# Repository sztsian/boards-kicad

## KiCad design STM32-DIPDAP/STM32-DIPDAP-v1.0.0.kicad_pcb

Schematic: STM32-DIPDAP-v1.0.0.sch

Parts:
C1, C3, C7, C8, C9, C10, C11, C12: 100nF; C_0805_2012Metric_Pad1.15x1.40mm_HandSolder
C2, C4: 10uF; C_0603_1608Metric_Pad1.05x0.95mm_HandSolder
C5, C6: 22pF; C_0603_1608Metric_Pad1.05x0.95mm_HandSolder
C13, C14: 18pF; C_0805_2012Metric_Pad1.15x1.40mm_HandSolder
CON1: USB_B_Micro; USB_Micro-B_Connector
CON2: IF; PinHeader_1x05_P2.54mm_Vertical
CON4: SWD-10-SMD; Connector_2x05_P2.54mm_Edge
CON5: GROVE-UART-I2C-PTH; PinHeader_1x04_P2.54mm_Vertical
LED1: RED; LED_0805_2012Metric_Pad1.15x1.40mm_HandSolder
LED2: BLUE; LED_0805_2012Metric_Pad1.15x1.40mm_HandSolder
LED3: GREEN; LED_0805_2012Metric_Pad1.15x1.40mm_HandSolder
R1, R11: 10K; R_0805_2012Metric_Pad1.15x1.40mm_HandSolder
R2, R14: 100K; R_0805_2012Metric_Pad1.15x1.40mm_HandSolder
R3, R5: 4.7K; R_0805_2012Metric_Pad1.15x1.40mm_HandSolder
R4, R7: 33R; R_0603_1608Metric_Pad1.05x0.95mm_HandSolder
R6: 100R; R_0603_1608Metric_Pad1.05x0.95mm_HandSolder
R8: 470R; R_0603_1608Metric_Pad1.05x0.95mm_HandSolder
R9, R10: 1.5K; R_0805_2012Metric_Pad1.15x1.40mm_HandSolder
SW1: SKRKAEE010
TP1, TP2, TP3, TP4, TP5, TP6, TP7, TP8: PTR1TP07R; TP07R
U2: TLV1117LV33DCYR; SOT223
U3: STM32F103CBT6; LQFP-48_7x7mm_P0.5mm
Y1: 8M; Crystal_SMD_5032-2Pin_5.0x3.2mm

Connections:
+3.3V: C3.1, C4.1, C8.1, C9.1, C10.1, C11.1, CON2.4, CON5.3, LED2.2, LED3.2, R2.1, R3.1, R11.1, U2.OUT(1), U2.OUT(2), U3.1, U3.9, U3.24, U3.36, U3.48
/AIN12_1: TP2.TP, U3.11
/AIN12_9: TP1.TP, U3.19
/I2C1_SCL: TP4.TP, U3.45
/I2C1_SDA: TP3.TP, U3.46
/I2C2_SCL: CON5.1, U3.21
/I2C2_SDA: CON5.2, U3.22
/IF_NRESET: C7.1, CON2.5, R2.2, U3.7
/IF_SWCLK: CON2.2, U3.37
/IF_SWDIO: CON2.1, U3.34
/LED_COM_GRN: R10.2, U3.41
/LED_DAP_BLUE: R9.2, U3.42
/LED_PWR_RED: R8.2, U3.30
/SPI1_MISO: TP8.TP, U3.16
/SPI1_MOSI: TP7.TP, U3.17
/SPI1_NSS: TP5.TP, U3.14
/SPI1_SCK: TP6.TP, U3.39
/TGT_NRESET: C12.1, CON4.10, R11.2, SW1.P$1, U3.18
/TGT_RX: CON4.8, U3.12
/TGT_SWCLK: CON4.4, U3.15, U3.26
/TGT_SWDIO: CON4.2, R6.2, U3.27
/TGT_SWO: CON4.6, U3.31
/TGT_TX: CON4.7, U3.13
/TGT_USB_D+: CON1.3 (D+), R4.2
/TGT_USB_D-: CON1.2 (D-), R7.2
GND: C1.2, C2.2, C3.2, C4.2, C5.2, C6.2, C7.2, C8.2, C9.2, C10.2, C11.2, C12.2, C13.2, C14.2, CON1.5 (GND), CON2.3, CON4.3, CON4.5, CON4.9, CON5.4, LED1.1, R1.1, R5.2, R14.1, SW1.P$2, U2.GND, U3.8, U3.20, U3.23, U3.35, U3.47
unnamed: C1.1, C2.1, CON1.1 (VBUS), U2.IN
unnamed: C5.1, U3.5, Y1.1
unnamed: C6.1, U3.6, Y1.2
unnamed: C13.1, R7.1, U3.32
unnamed: C14.1, R4.1, U3.33
unnamed: LED1.2, R8.1
unnamed: LED2.1, R9.1
unnamed: LED3.1, R10.1
unnamed: R1.2, U3.2
unnamed: R3.2, R5.1, U3.10
unnamed: R6.1, U3.25
unnamed: R14.2, U3.44

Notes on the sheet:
8MHz
DAPLink Interface STM32F103CBT6

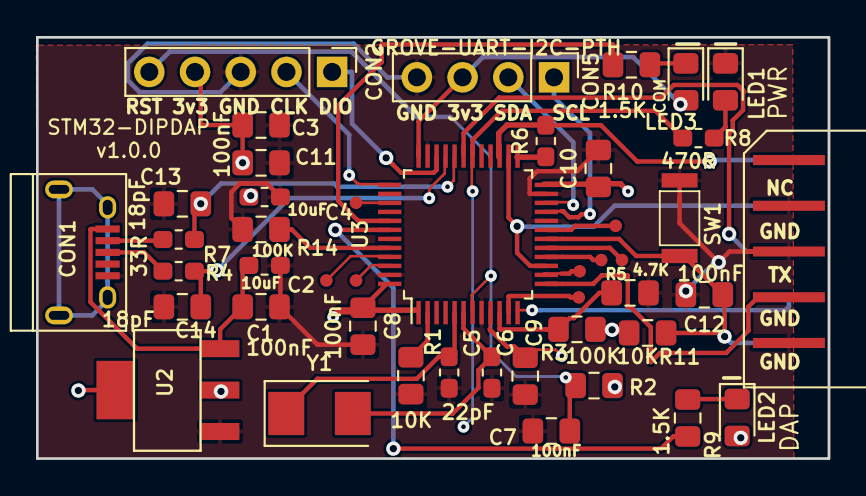
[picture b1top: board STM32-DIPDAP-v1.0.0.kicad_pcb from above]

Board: 2 copper layers, 44.0 x 23.4 mm, 45 parts (0 on the bottom side), 38 nets.

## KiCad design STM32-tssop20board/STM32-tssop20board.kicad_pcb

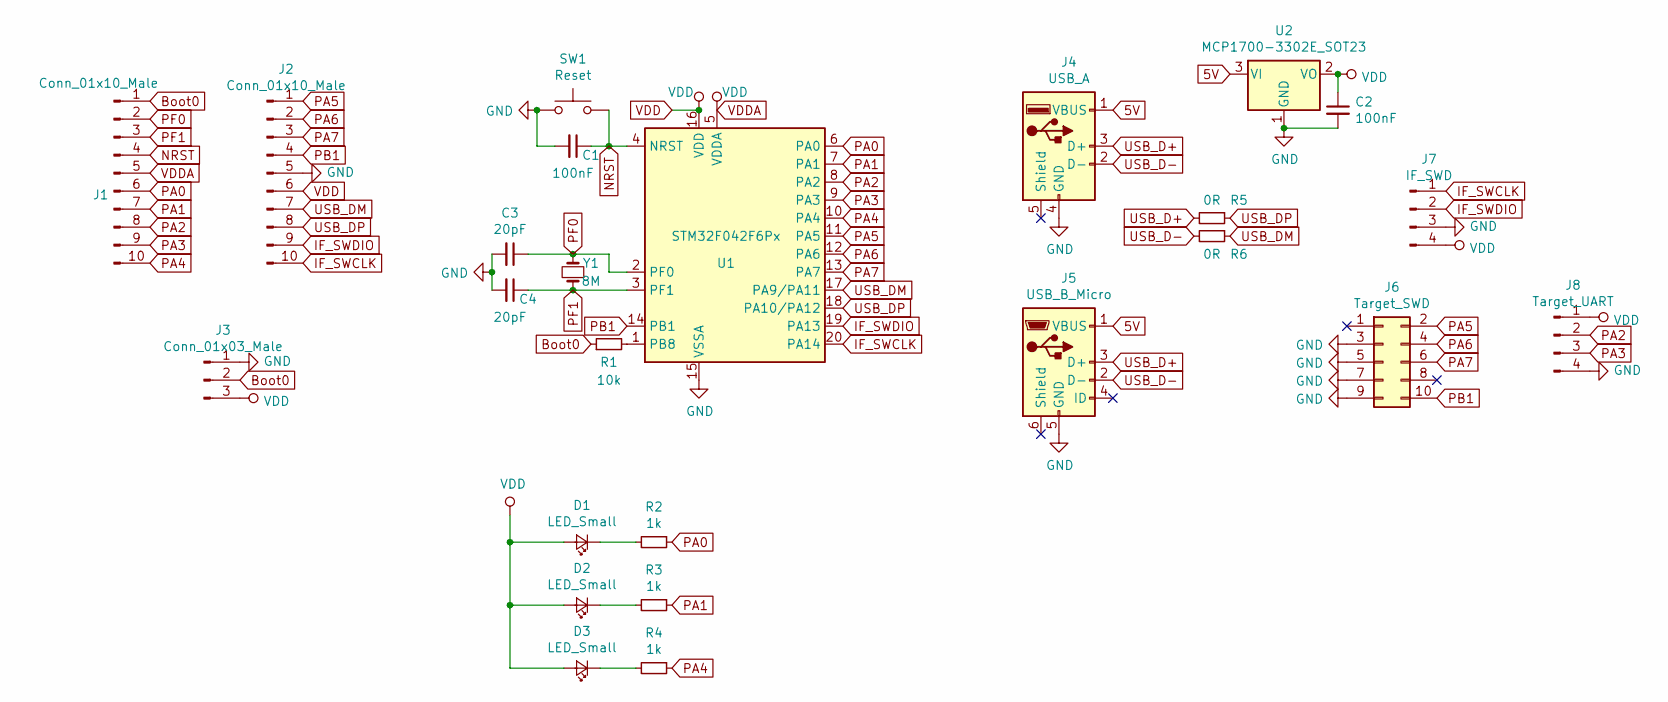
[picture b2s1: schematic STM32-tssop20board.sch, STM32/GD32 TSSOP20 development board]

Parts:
C1, C2: 100nF; C_0805_2012Metric_Pad1.15x1.40mm_HandSolder
C3, C4: 20pF; C_0805_2012Metric_Pad1.15x1.40mm_HandSolder
D1, D2, D3: LED_Small; LED_0805_2012Metric_Pad1.15x1.40mm_HandSolder
J1, J2: Conn_01x10_Male; PinHeader_1x10_P2.54mm_Vertical
J3: Conn_01x03_Male; PinHeader_1x03_P2.54mm_Vertical
J4: USB_A; USB_A_Plug
J5: USB_B_Micro; USB_Micro-B_Wuerth_614105150721_Vertical
J6: Target_SWD; PinHeader_2x05_P2.54mm_Vertical
J7: IF_SWD; PinHeader_1x04_P2.54mm_Vertical
J8: Target_UART; PinHeader_1x04_P2.54mm_Vertical
R1: 10k; R_0805_2012Metric_Pad1.15x1.40mm_HandSolder
R2, R3, R4: 1k; R_0805_2012Metric_Pad1.15x1.40mm_HandSolder
R5, R6: 0R; R_0805_2012Metric_Pad1.15x1.40mm_HandSolder
SW1: Reset; smd_push
U1: STM32F042F6Px; TSSOP-20_4.4x6.5mm_P0.65mm
U2: MCP1700-3302E_SOT23; SOT-23
Y1: 8M; Crystal_SMD_5032-2Pin_5.0x3.2mm_HandSoldering

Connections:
5V: J4.1 (VBUS), J5.1 (VBUS), U2.3 (VI)
Boot0: J1.1, J3.2, R1.1
GND: C1.2, C2.2, C3.2, C4.2, J2.5, J3.1, J4.4 (GND), J5.5 (GND), J6.3, J6.5, J6.7, J6.9, J7.3, J8.4, SW1.1, U1.15 (VSSA), U2.1 (GND)
IF_SWCLK: J2.10, J7.1, U1.20 (PA14)
IF_SWDIO: J2.9, J7.2, U1.19 (PA13)
NRST: C1.1, J1.4, SW1.2, U1.4 (NRST)
unnamed: D1.1 (K), R2.2
unnamed: D2.1 (K), R3.2
unnamed: D3.1 (K), R4.2
unnamed: R1.2, U1.1 (PB8)
PA0: J1.6, R2.1, U1.6 (PA0)
PA1: J1.7, R3.1, U1.7 (PA1)
PA2: J1.8, J8.2, U1.8 (PA2)
PA3: J1.9, J8.3, U1.9 (PA3)
PA4: J1.10, R4.1, U1.10 (PA4)
PA5: J2.1, J6.2, U1.11 (PA5)
PA6: J2.2, J6.4, U1.12 (PA6)
PA7: J2.3, J6.6, U1.13 (PA7)
PB1: J2.4, J6.10, U1.14 (PB1)
PF0: C3.1, J1.2, U1.2 (PF0), Y1.2
PF1: C4.1, J1.3, U1.3 (PF1), Y1.1
USB_D+: J4.3 (D+), J5.3 (D+), R5.2
USB_D-: J4.2 (D-), J5.2 (D-), R6.2
USB_DM: J2.7, R6.1, U1.17 (PA9/PA11)
USB_DP: J2.8, R5.1, U1.18 (PA10/PA12)
VDD: C2.1, D1.2 (A), D2.2 (A), D3.2 (A), J1.5, J2.6, J3.3, J7.4, J8.1, U1.5 (VDDA), U1.16 (VDD), U2.2 (VO)

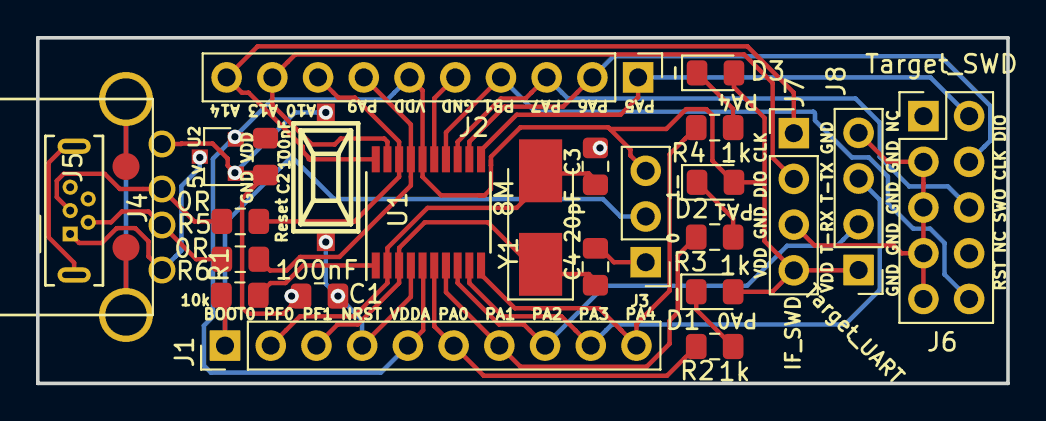
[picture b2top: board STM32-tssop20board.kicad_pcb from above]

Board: 2 copper layers, 53.9 x 19.2 mm, 25 parts (0 on the bottom side), 26 nets.

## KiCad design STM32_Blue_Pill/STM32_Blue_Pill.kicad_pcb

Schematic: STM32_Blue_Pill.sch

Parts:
C1, C2, C3, C11: 20p; C_0603_1608Metric_Pad1.05x0.95mm_HandSolder
C4: 1u; C_0603_1608Metric_Pad1.05x0.95mm_HandSolder
C5, C6, C7: 0.1u; C_0603_1608Metric_Pad1.05x0.95mm_HandSolder
C8: 10n; C_0603_1608Metric_Pad1.05x0.95mm_HandSolder
C9: 2.2u; C_0603_1608Metric_Pad1.05x0.95mm_HandSolder
C10: 100nF; C_0603_1608Metric_Pad1.05x0.95mm_HandSolder
D1: LED2; LED_0603_1608Metric_Pad1.05x0.95mm_HandSolder
D2: LED_PWR; LED_0603_1608Metric_Pad1.05x0.95mm_HandSolder
J1: BootJumper; PinHeader_2x03_P2.54mm_Vertical
J2, J3: Conn_01x20; PinHeader_1x20_P2.54mm_Vertical
J4: Conn_02x05_Odd_Even; PinHeader_2x05_P2.54mm_Horizontal
J7: USB_B_Micro; USB_Micro-B_Connector
R1, R2: 510R; R_0603_1608Metric_Pad1.05x0.95mm_HandSolder
R3: 1M; R_0603_1608Metric_Pad1.05x0.95mm_HandSolder
R4: 1.5K; R_0603_1608Metric_Pad1.05x0.95mm_HandSolder
R5: 10k; R_0603_1608Metric_Pad1.05x0.95mm_HandSolder
R7: 0R; R_0805_2012Metric_Pad1.15x1.40mm_HandSolder
R9, R10: 22; R_0603_1608Metric_Pad1.05x0.95mm_HandSolder
SW1: SW_Push; smd_push
U1: MCP1700-3302E_SOT23; SOT-23
U4: STM32F103C8Tx; LQFP-48_7x7mm_P0.5mm
Y1: 8M; Crystal_SMD_5032-2Pin_5.0x3.2mm
Y2: 32.768K; Crystal_SMD_3215-2Pin_3.2x1.5mm

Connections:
5V: J3.3, J7.1 (VBUS), R4.2, U1.3
BOOT0: J1.3, U4.44 (BOOT0)
BOOT1: J1.4, U4.20 (PB2)
GND: C1.2, C2.2, C3.2, C4.1, C5.1, C6.1, C7.1, C8.2, C9.2, C10.2, C11.2, J1.5, J1.6, J2.19, J2.20, J3.2, J4.3, J4.5, J7.5 (GND), J7.6 (Shield), R2.2, SW1.2, U1.1, U4.8 (VSSA), U4.23 (VSS), U4.35 (VSS), U4.47 (VSS)
NRST: C4.2, J2.17, J4.10, R5.1, SW1.1, U4.7 (NRST)
unnamed: C2.1, R3.1, U4.5 (PD0), Y1.1
unnamed: C3.1, R3.2, U4.6 (PD1), Y1.2
unnamed: C8.1, C9.1, R7.2, U4.9 (VDDA)
unnamed: D1.1 (K), R1.1
unnamed: D2.1 (K), R2.1
PA0: J2.5, U4.10 (PA0)
PA1: J2.6, U4.11 (PA1)
PA2: J2.7, U4.12 (PA2)
PA3: J2.8, U4.13 (PA3)
PA4: J2.9, U4.14 (PA4)
PA5: J2.10, U4.15 (PA5)
PA6: J2.11, U4.16 (PA6)
PA7: J2.12, U4.17 (PA7)
PA8: J3.16, U4.29 (PA8)
PA9: J3.15, U4.30 (PA9)
PA10: J3.14, U4.31 (PA10)
PA11: J3.13, R9.2, U4.32 (PA11)
PA12: J3.12, R4.1, R10.2, U4.33 (PA12)
PA13-SWDIO-TMS: J4.2, U4.34 (PA13)
PA14-SWCLK-TCK: J4.4, U4.37 (PA14)
PA15-TDI: J3.11, J4.8, U4.38 (PA15)
PB0: J2.13, U4.18 (PB0)
PB1: J2.14, U4.19 (PB1)
PB3-TDO: J3.10, J4.6, U4.39 (PB3)
PB4: J3.9, U4.40 (PB4)
PB5: J3.8, U4.41 (PB5)
PB6: J3.7, U4.42 (PB6)
PB7: J3.6, U4.43 (PB7)
PB8: J3.5, U4.45 (PB8)
PB9: J3.4, U4.46 (PB9)
PB10: J2.15, U4.21 (PB10)
PB11: J2.16, U4.22 (PB11)
PB12: J3.20, U4.25 (PB12)
PB13: J3.19, U4.26 (PB13)
PB14: J3.18, U4.27 (PB14)
PB15: J3.17, U4.28 (PB15)
PC13: J2.2, R1.2, U4.2 (PC13)
PC14: C1.1, J2.3, U4.3 (PC14), Y2.1
PC15: C11.1, J2.4, U4.4 (PC15), Y2.2
USB-D+: J7.3 (D+), R10.1
USB-D-: J7.2 (D-), R9.1
VBAT: J2.1, U4.1 (VBAT)

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
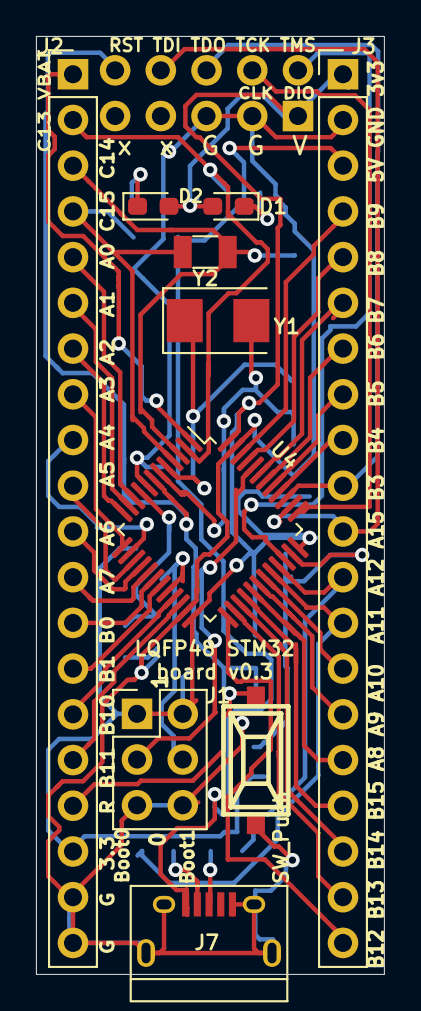
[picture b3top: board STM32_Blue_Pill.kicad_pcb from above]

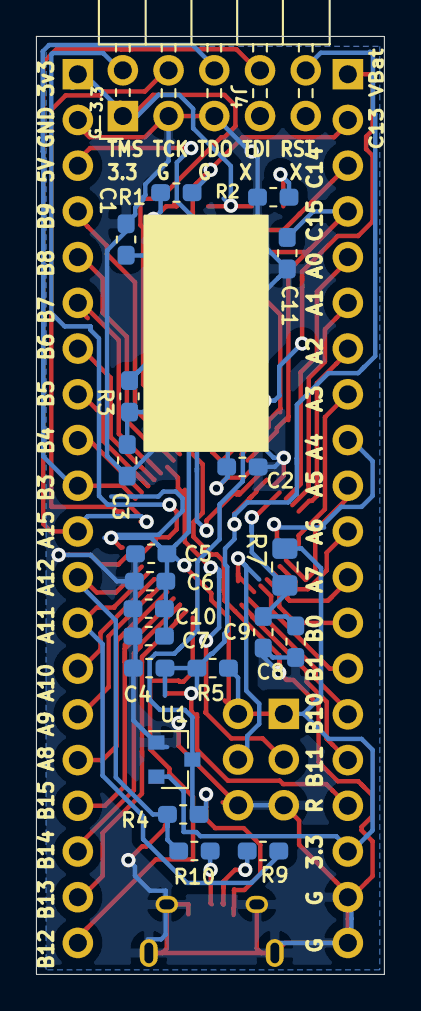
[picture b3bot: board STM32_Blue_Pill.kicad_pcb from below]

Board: 2 copper layers, 19.3 x 52.1 mm, 31 parts (21 on the bottom side), 48 nets.

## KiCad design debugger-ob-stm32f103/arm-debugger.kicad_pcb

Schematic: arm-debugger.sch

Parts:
C1, C2: 15pF; C_0805_2012Metric_Pad1.15x1.40mm_HandSolder
C3, C4, C5, C6, C7, C8, C9: 100nF; C_0805_2012Metric_Pad1.15x1.40mm_HandSolder
D1: LED; LED_0805_2012Metric_Pad1.15x1.40mm_HandSolder
J1: USB_A; USB_A_Plug
J2: Conn_02x05_Odd_Even; PinHeader_2x05_P2.54mm_Vertical
J3: Flash; PinHeader_1x03_P2.54mm_Vertical
J4: VDD; PinHeader_1x01_P2.54mm_Vertical
R1: 1k; R_0805_2012Metric_Pad1.15x1.40mm_HandSolder
R2: 1k5; R_0805_2012Metric_Pad1.15x1.40mm_HandSolder
R3, R4: 22R; R_0805_2012Metric_Pad1.15x1.40mm_HandSolder
R5, R6, R7, R8, R9: 100; R_0603_1608Metric_Pad1.05x0.95mm_HandSolder
R10: 10k; R_0805_2012Metric_Pad1.15x1.40mm_HandSolder
U1: STM32F103C8Tx; LQFP-48_7x7mm_P0.5mm
U2: 6206; SOT-23
Y1: 8M; Crystal_SMD_5032-2Pin_5.0x3.2mm

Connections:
5V: C9.1, J1.1, U2.3
CLK_FLASH: J3.1, U1.37 (PA14)
DIO_FLASH: J3.2, U1.34 (PA13)
Debugger-TCK-IN: J2.4, R8.2, U1.13 (PA3)
Debugger-TCK-OUT: R8.1, U1.15 (PA5), U1.26 (PB13)
Debugger-TDI-IN: J2.8, R6.2, U1.18 (PB0)
Debugger-TDI-OUT: R6.1, U1.27 (PB14)
Debugger-TDO-IN: J2.6, R10.1, U1.16 (PA6), U1.28 (PB15), U1.31 (PA10)
Debugger-TMS-IN: J2.2, R7.2, U1.14 (PA4)
Debugger-TMS-OUT: R7.1, U1.17 (PA7)
Debugger-TRES-IN: R9.2, U1.12 (PA2)
Debugger-TRES-OUT: R9.1, U1.11 (PA1)
Debugger-TRST-IN: J2.10, R5.2, U1.19 (PB1)
Debugger-TRST-OUT: R5.1, U1.10 (PA0)
GND: C1.2, C2.2, C3.2, C4.1, C5.1, C6.1, C7.1, C8.2, C9.2, J1.4, J2.3, J2.5, J3.3, U1.8 (VSSA), U1.20 (PB2), U1.23 (VSS), U1.35 (VSS), U1.44 (BOOT0), U1.47 (VSS), U2.1
unnamed: C1.1, U1.5 (PD0), Y1.1
unnamed: C2.1, U1.6 (PD1), Y1.2
unnamed: C3.1, U1.7 (NRST)
unnamed: D1.1 (K), R1.2
unnamed: R1.1, U1.25 (PB12)
unnamed: R2.2, U1.30 (PA9)
unnamed: R3.2, U1.32 (PA11)
unnamed: R4.2, U1.33 (PA12)
USB-D+: J1.3, R2.1, R4.1
USB-D-: J1.2, R3.1
VDD: C4.2, C5.2, C6.2, C7.2, C8.1, D1.2 (A), J4.1, R10.2, U1.1 (VBAT), U1.9 (VDDA), U1.24 (VDD), U1.36 (VDD), U1.48 (VDD), U2.2

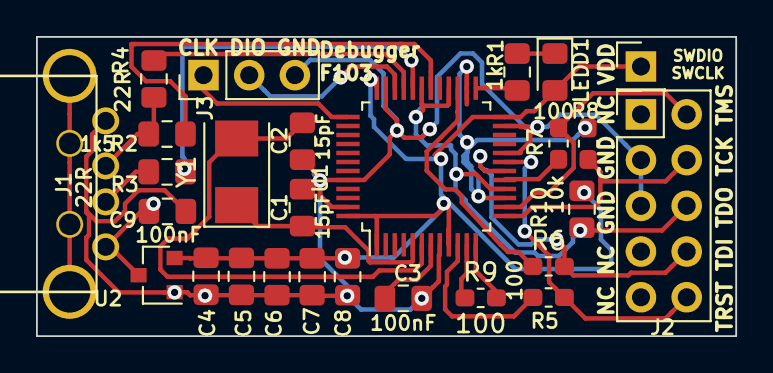
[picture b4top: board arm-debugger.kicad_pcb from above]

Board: 2 copper layers, 38.9 x 16.6 mm, 27 parts (0 on the bottom side), 26 nets.

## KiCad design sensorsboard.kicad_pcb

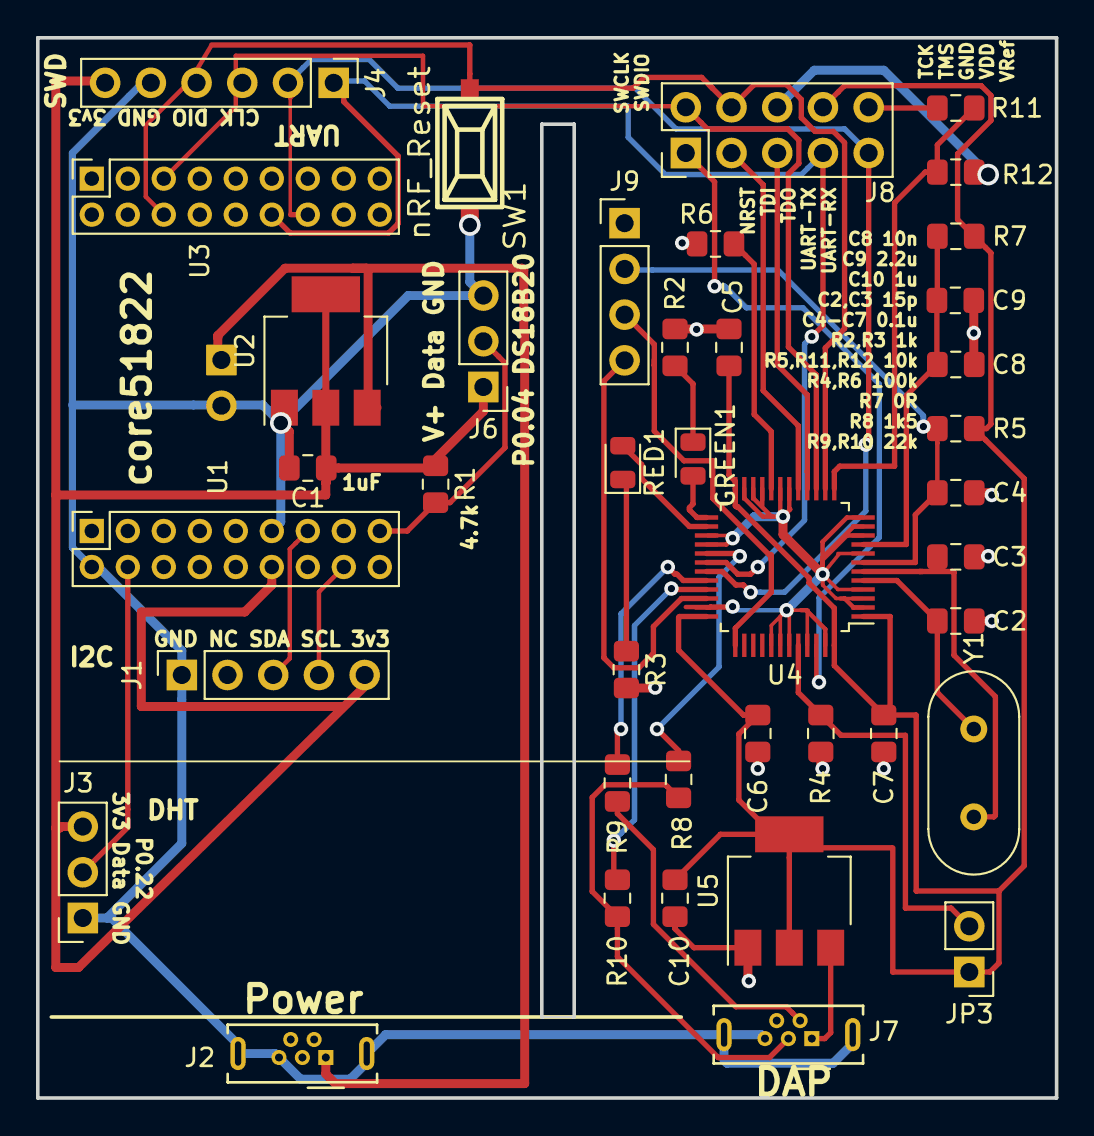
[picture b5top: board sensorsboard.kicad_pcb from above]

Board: 2 copper layers, 56.6 x 58.9 mm, 41 parts (1 on the bottom side), 35 nets.

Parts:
C1, C10: 1uF; C_0805_2012Metric_Pad1.15x1.40mm_HandSolder
C2, C3: 15p; C_0805_2012Metric_Pad1.15x1.40mm_HandSolder
C4, C5, C6, C7: 0.1u; C_0805_2012Metric_Pad1.15x1.40mm_HandSolder
C8: 10n; C_0805_2012Metric_Pad1.15x1.40mm_HandSolder
C9: 2.2u; C_0805_2012Metric_Pad1.15x1.40mm_HandSolder
GREEN1: LEDCHIPLED0603; LED_0805_2012Metric
J1: Conn_01x05_Female; PinSocket_1x05_P2.54mm_Vertical
J2, J7: USB_B_Micro; USB_Micro-B_Wuerth_614105150721_Vertical
J3: Conn_01x03_Female; PinSocket_1x03_P2.54mm_Vertical
J4: Conn_01x06_Male; PinHeader_1x06_P2.54mm_Vertical
J5: Conn_01x02_Male; PinHeader_1x02_P2.54mm_Horizontal
J6: Conn_01x03_Male; PinHeader_1x03_P2.54mm_Vertical
J8: Conn_02x05_Odd_Even; PinHeader_2x05_P2.54mm_Vertical
J9: Self_Flash; PinHeader_1x04_P2.54mm_Vertical
JP3: Jmp-2SMD-NO; PinHeader_1x02_P2.54mm_Vertical
R1: 4.7k; R_0805_2012Metric_Pad1.15x1.40mm_HandSolder
R2, R3: 1k; R_0805_2012Metric_Pad1.15x1.40mm_HandSolder
R4, R6: 100k; R_0805_2012Metric_Pad1.15x1.40mm_HandSolder
R5, R11, R12: 10k; R_0805_2012Metric_Pad1.15x1.40mm_HandSolder
R7: 0R; R_0805_2012Metric_Pad1.15x1.40mm_HandSolder
R8: 1k5; R_0805_2012Metric_Pad1.15x1.40mm_HandSolder
R9, R10: 22; R_0805_2012Metric_Pad1.15x1.40mm_HandSolder
RED1: LEDCHIPLED_0603; LED_0805_2012Metric
SW1: nRF_Reset; smd_push
U1: Waveshare_Core51822_P2; PinSocket_2x09_P2.00mm_Vertical
U2, U5: AMS1117-3.3; SOT-223-3_TabPin2
U3: Waveshare_Core51822_P3; PinSocket_2x09_P2.00mm_Vertical
U4: STM32F103C8Tx; LQFP-48_7x7mm_P0.5mm
Y1: 8M Crystal; Crystal_HC49-U_Vertical

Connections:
+3V3: C1.1, J1.5, J3.3, J4.6, J6.1, R1.1, U1.12, U2.2
+5V: J2.1, J5.1, U2.3
DHT_OUT: J3.2, U1.4
DS_OUT: J6.2, R1.2, U1.17
GND: C1.2, C2.2, C3.2, C4.1, C5.1, C6.1, C7.1, C8.2, C9.2, C10.2, J1.1, J2.5, J2.6, J3.1, J4.5, J5.2, J6.3, J7.5, J7.6, J8.6, J9.1, R2.2, R3.2, R4.2, R6.2, R12.1, SW1.2, U1.2, U1.11, U2.1, U4.2, U4.3, U4.4, U4.8, U4.10, U4.11, U4.12, U4.18, U4.19, U4.21, U4.22, U4.23, U4.27, U4.28, U4.35, U4.41, U4.42, U4.43, U4.45, U4.47, U5.1
I2C_SCL: J1.4, U1.16
I2C_SDA: J1.3, U1.13
unnamed: C2.1, U4.5, Y1.1
unnamed: C3.1, U4.6, Y1.2
unnamed: C8.1, C9.1, R7.2, U4.9
unnamed: GREEN1.1, R2.1
unnamed: GREEN1.2, U4.25
unnamed: J7.1, U5.3
unnamed: J8.10, R11.2
unnamed: JP3.2, R4.1, U4.44
unnamed: R3.1, RED1.1
unnamed: R6.1, U4.20
unnamed: R8.2, U4.29
unnamed: R9.2, U4.32
unnamed: R10.2, U4.33
unnamed: RED1.2, U4.26
PA3-VREF: R11.1, R12.2, U4.13
PA4-SWDIO-TMS: J4.4, J8.4, SW1.1, U3.6, U4.14
PA5-SWCLK-TCK: J4.3, J8.2, U3.5, U4.15
PA6-SWO-TDO: J8.5, U4.16
PA7-TDI: J8.3, U4.17
PA9-TX: J4.1, J8.7, U3.12, U4.30
PA10-RX: J4.2, J8.9, U3.14, U4.31
PA13-SWDIO: J9.4, U4.34
PA14-SWCLK: J9.3, U4.37
PB9-NRESET: J8.1, U4.46
RESET1-TP3: C4.2, J9.2, R5.1, U4.7
USB-D+: J7.3, R8.1, R10.1
USB-D-: J7.2, R9.1
VDD: C5.2, C6.2, C7.2, C10.1, J8.8, JP3.1, R5.2, R7.1, U4.1, U4.24, U4.36, U4.48, U5.2
